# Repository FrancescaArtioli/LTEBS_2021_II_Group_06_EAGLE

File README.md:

# LTEBS_2021_II_Group_06_EAGLE
Authors: Artioli Francesca, Parrella Giovanni

This repository contains a complete Eagle project of a custom PCB, designed in order to ease the assessment of the performance of the PSoC-5LP microcontroller. 
In particular, the repository contains the schematic (.sch), the board (.brd) and the design-rule-check file (.dru) based on technical requirements by MDSrl. 

The PCB embeds the developement kit for PSoC-5LP (namely CY8CKIT-059_TARGET) together with sensors and additional components required to conduct the proper testing.

### Sensors (from SparkFun-Sensors.lbr) 
-	Light Sensor

	PHOTOCELLPTH - PHOTOCELL

- 	Analog Temperature Sensor

	TMP36GT9 - TO-92
  
### Libraries 

- SparkFun-Eagle-Libraries, downloaded from https://github.com/sparkfun/SparkFun-Eagle-Libraries

- CY8KIT-059.lbr, downloaded from https://github.com/dado93/Cypress-Eagle

- Group_06_Library.lbr, a custom library for TMUX1208 and TCA9546A from Texas Instruments.

### Notes on Group_06_Library.lbr
-	We have decided to design the pads for both components TMUX1208 (package QFN-16) and TCA9546A (package TSSOP-16) with a rectangular shape. 
-	Regarding package dimension of component TMUX1208 we have decided to keep the middle value between maximum and minimum dimension (1.80mmx2.60mm).
-	Regarding package dimension of component TCA9546A we have decided to keep the middle value between maximum and minimum dimension (4.4mmx5mm).
-	In both the components' footprint we have added the profile silkscreen in a way that it wouldn't provide a stop-mask error in the DRC (even if we have not considered stop mask error when running the DRC file, as suggested). 

### Notes on Group_06.sch 
-	Schematic is divided into two pages.

### Notes on Group_06.brd
-	The trace dimension was set to 10 mils for all traces of the PCB, except for those connecting to the mux which were set to 8 mils to avoid clearance errors.
-	Final board dimensions are : 60.83 mm x 72.39 mm

### Notes on Group_06.dru
-	We followed the requirements from the MDSrl.
-	The "check stop mask" option in the MISC section was not selected, as suggested.

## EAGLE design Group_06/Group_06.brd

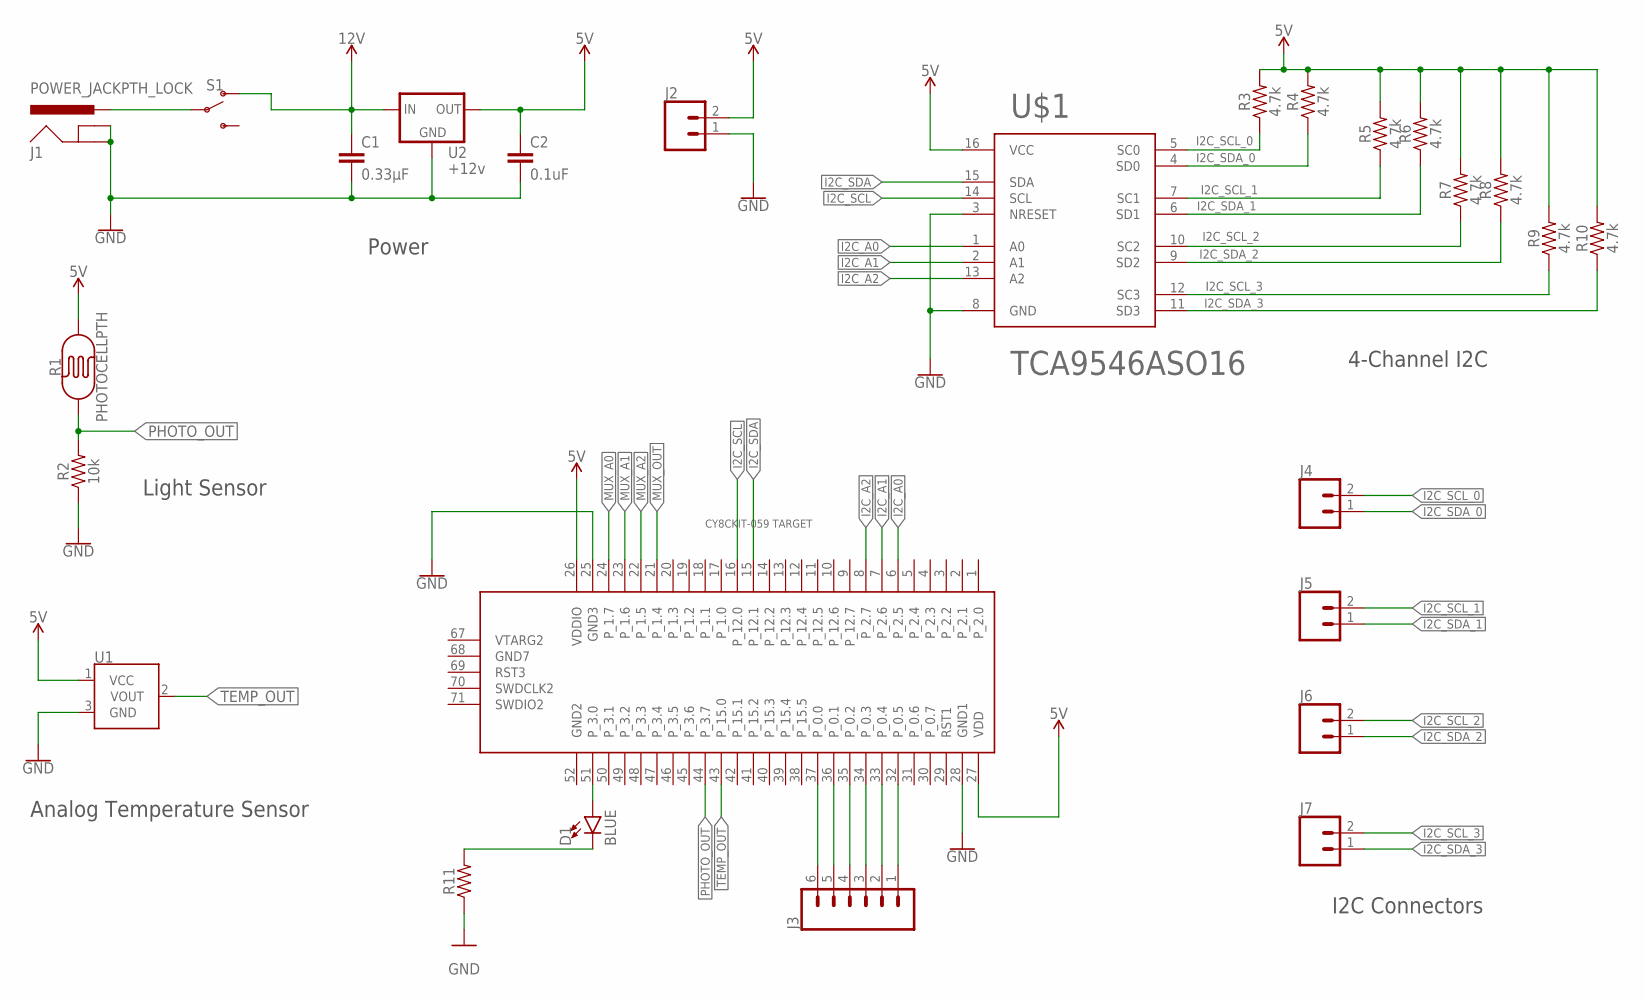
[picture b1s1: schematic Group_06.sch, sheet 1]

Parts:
C1: 0.33µF; 0805
C2: 0.1uF; CAP-PTH-SMALL-KIT
D1: BLUE; LED-1206
J1: POWER_JACKPTH_LOCK; POWER_JACK_PTH_LOCK
J2, J4, J5, J6, J7: CONN_02; 1X02
J3: CONN_06LOCK; 1X06_LOCK
R1: PHOTOCELLPTH; PHOTOCELL
R2: 10k; 0603
R3, R4, R5, R6, R7, R8, R9, R10: 4.7k; 0603
R11: AXIAL-0.3
S1: SWITCH-SPDT-PTH-11.6X4.0MM; SWITCH_SPDT_PTH_11.6X4.0MM
U1: TMP36GT9; TO-92
U2: +12v; TO-252
U$1: TCA9546ASO16; TSSOP-16
U$2: CY8CKIT-059_TARGET

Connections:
5V: C2.1, J2.2, R1.2, R3.2, R4.2, R5.2, R6.2, R7.2, R8.2, R9.2, R10.2, U1.1 (VCC), U2.2 (OUT), U$1.16 (VCC), U$2.26 (VDDIO), U$2.27 (VDD); also elsewhere on the board
12V: C1.1, S1.1 (O), U2.1 (IN)
GND: C1.2, C2.2, J1.GND, J1.GNDBREAK, J2.1, R2.1, R11.P$1 (1), U1.3 (GND), U2.3 (GND), U$1.3 (NRESET), U$1.8 (GND), U$2.25 (GND3), U$2.28 (GND1); also elsewhere on the board
I2C_A0: U$1.1 (A0), U$2.6 (P_2.5)
I2C_A1: U$1.2 (A1), U$2.7 (P_2.6)
I2C_A2: U$1.13 (A2), U$2.8 (P_2.7)
I2C_SCL: U$1.14 (SCL), U$2.16 (P_12.0)
I2C_SCL_0: J4.2, R3.1, U$1.5 (SC0)
I2C_SCL_1: J5.2, R5.1, U$1.7 (SC1)
I2C_SCL_2: J6.2, R7.1, U$1.10 (SC2)
I2C_SCL_3: J7.2, R9.1, U$1.12 (SC3)
I2C_SDA: U$1.15 (SDA), U$2.15 (P_12.1)
I2C_SDA_0: J4.1, R4.1, U$1.4 (SD0)
I2C_SDA_1: J5.1, R6.1, U$1.6 (SD1)
I2C_SDA_2: J6.1, R8.1, U$1.9 (SD2)
I2C_SDA_3: J7.1, R10.1, U$1.11 (SD3)
MUX_A0: U$2.24 (P_1.7); also elsewhere on the board
MUX_A1: U$2.23 (P_1.6); also elsewhere on the board
MUX_A2: U$2.22 (P_1.5); also elsewhere on the board
MUX_OUT: U$2.21 (P_1.4); also elsewhere on the board
unnamed: J1.PWR, S1.2
unnamed: D1.A, U$2.51 (P_3.0)
unnamed: D1.C, R11.P$2 (2)
unnamed: J3.6, U$2.37 (P_0.0)
unnamed: J3.5, U$2.36 (P_0.1)
unnamed: J3.4, U$2.35 (P_0.2)
unnamed: J3.3, U$2.34 (P_0.3)
unnamed: J3.2, U$2.33 (P_0.4)
unnamed: J3.1, U$2.32 (P_0.5)
PHOTO_OUT: R1.1, R2.2, U$2.44 (P_3.7)
TEMP_OUT: U1.2 (VOUT), U$2.43 (P_15.0)

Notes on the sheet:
I2C Connectors
4-Channel I2C
Power
Light Sensor
Analog Temperature Sensor

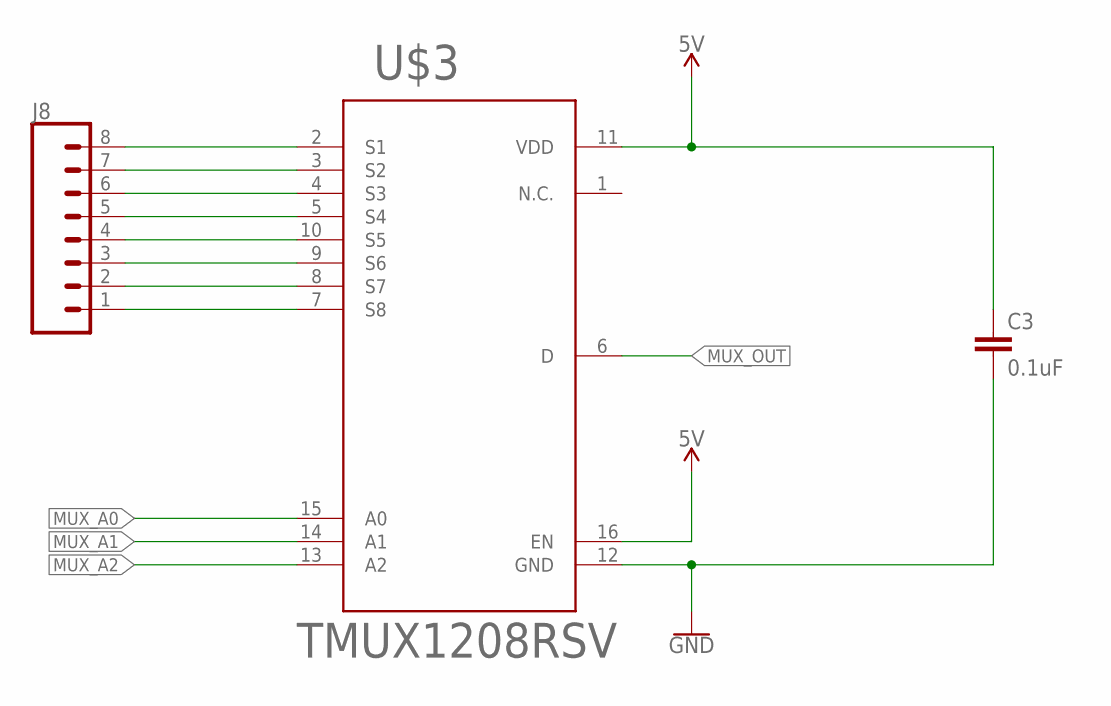
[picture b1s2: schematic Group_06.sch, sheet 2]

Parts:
C3: 0.1uF; CAP-PTH-SMALL-KIT
J8: CONN_08LOCK; 1X08_LOCK
U$3: TMUX1208RSV; QFN-16

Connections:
5V: C3.1, U$3.11 (VDD), U$3.16 (EN); also elsewhere on the board
GND: C3.2, U$3.12 (GND); also elsewhere on the board
MUX_A0: U$3.15 (A0); also elsewhere on the board
MUX_A1: U$3.14 (A1); also elsewhere on the board
MUX_A2: U$3.13 (A2); also elsewhere on the board
MUX_OUT: U$3.6 (D); also elsewhere on the board
unnamed: J8.8, U$3.2 (S1)
unnamed: J8.7, U$3.3 (S2)
unnamed: J8.6, U$3.4 (S3)
unnamed: J8.5, U$3.5 (S4)
unnamed: J8.4, U$3.10 (S5)
unnamed: J8.3, U$3.9 (S6)
unnamed: J8.2, U$3.8 (S7)
unnamed: J8.1, U$3.7 (S8)

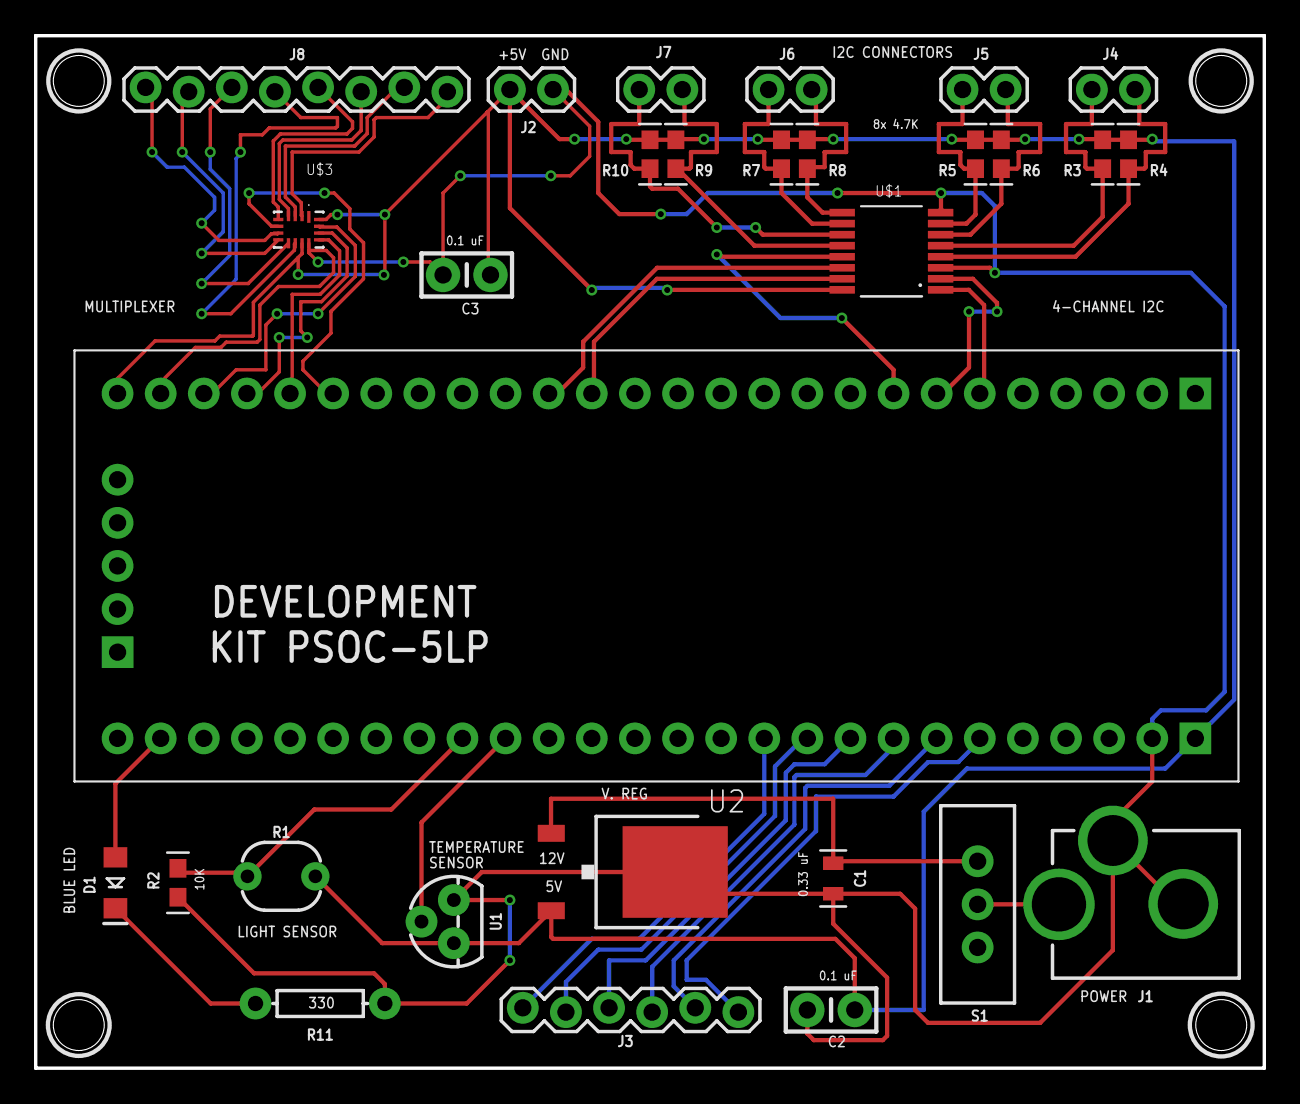
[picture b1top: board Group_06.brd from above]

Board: 2 copper layers, 72.4 x 60.8 mm, 29 parts (0 on the bottom side), 39 nets.

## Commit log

2021-03-18 TMUX1208_Library
2021-03-18 TCA9546A_Library and origin point
2021-03-18 Sch_5components and variant name
2021-03-19 I2C_Connectors and Names
2021-03-19 Adding TMUX1208
2021-03-19 Change microcontroller and fixing connection problem
2021-03-19 DRU file
2021-03-19 first try board
2021-03-20 Board Layout 1
2021-03-20 Board Layout 2
2021-03-20 Board Layout 3
2021-03-20 Routing 1
2021-03-20 Routing 2
2021-03-21 Routing_mux_gio
2021-03-21 MUX 1
2021-03-21 Routing_mux
2021-03-21 Routing mux 3
2021-03-22 Routing optimization and correct placing tNames
2021-03-22 Dev mux fra (#1)
    * MUX 1
    * Routing optimization and correct placing tNames
2021-03-22 update DRC file
2021-03-22 Silkscreen labels and fixing stop mask interferences
2021-03-22 update silkscreen and fix library problem
2021-03-22 Silkscreen (#4)
    * update DRC file
    * Silkscreen labels and fixing stop mask interferences
    * update silkscreen and fix library problem
2021-03-22 fixing power and silkscreen
2021-03-22 fixing power and silkscreen (#5)
2021-03-23 Change J8
2021-03-23 Adding component silkscreen
2021-03-23 Dev corrections (#6)
    * Change J8
    * Adding component silkscreen
2021-03-23 shrinking the board
2021-03-23 shrinking the board (#7)
2021-03-23 update board
2021-03-24 correction component TCA9546A
2021-03-24 correction component TCA9546A (#8)
2021-03-24 Correction component TMUX1208
2021-03-24 Change Layer TMUX1208
2021-03-24 Library corrections (#9)
    * Correction component TMUX1208
    * Change Layer TMUX1208
2021-03-25 Update vias
2021-03-25 Change MUX name position
2021-03-25 DRC description and fixing silkscreen
2021-03-26 GND traces and silkscreen dimensions
2021-03-26 GND traces and silkscreen dimensions (#10)
2021-03-26 Final version

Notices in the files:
parts and their libraries:
SparkFun-Sensors: Licensing: Creative Commons ShareAlike 4.0 International - https://creativecommons.org/licenses/by-sa/4.0
